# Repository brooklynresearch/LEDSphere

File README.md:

# LEDSphere
Code for controlling a matrix of LED Spheres

## Embedded Code
This folder is for any code that will be needed for the individual spheres

## Controller Code
This folder is for any code that will control full set of animations

## Eagle Files
This folder is for any PCB that will need to be designed for the spheres and control

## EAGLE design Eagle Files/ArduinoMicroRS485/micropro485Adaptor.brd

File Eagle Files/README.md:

# Eagle Files
CAD files for PCB Designs.  All designs are currently tailored for the othermill and are more or less a one layer.

## Pixel Controller
Files for the individual Sphere.

## ENC28J60
Files for the ENC28J60 Breakout

## PoE Supply
Files to convert the PoE power to +5V

## To Do
* Determine Communications Protocol
* Design for SMD components and reduce profile

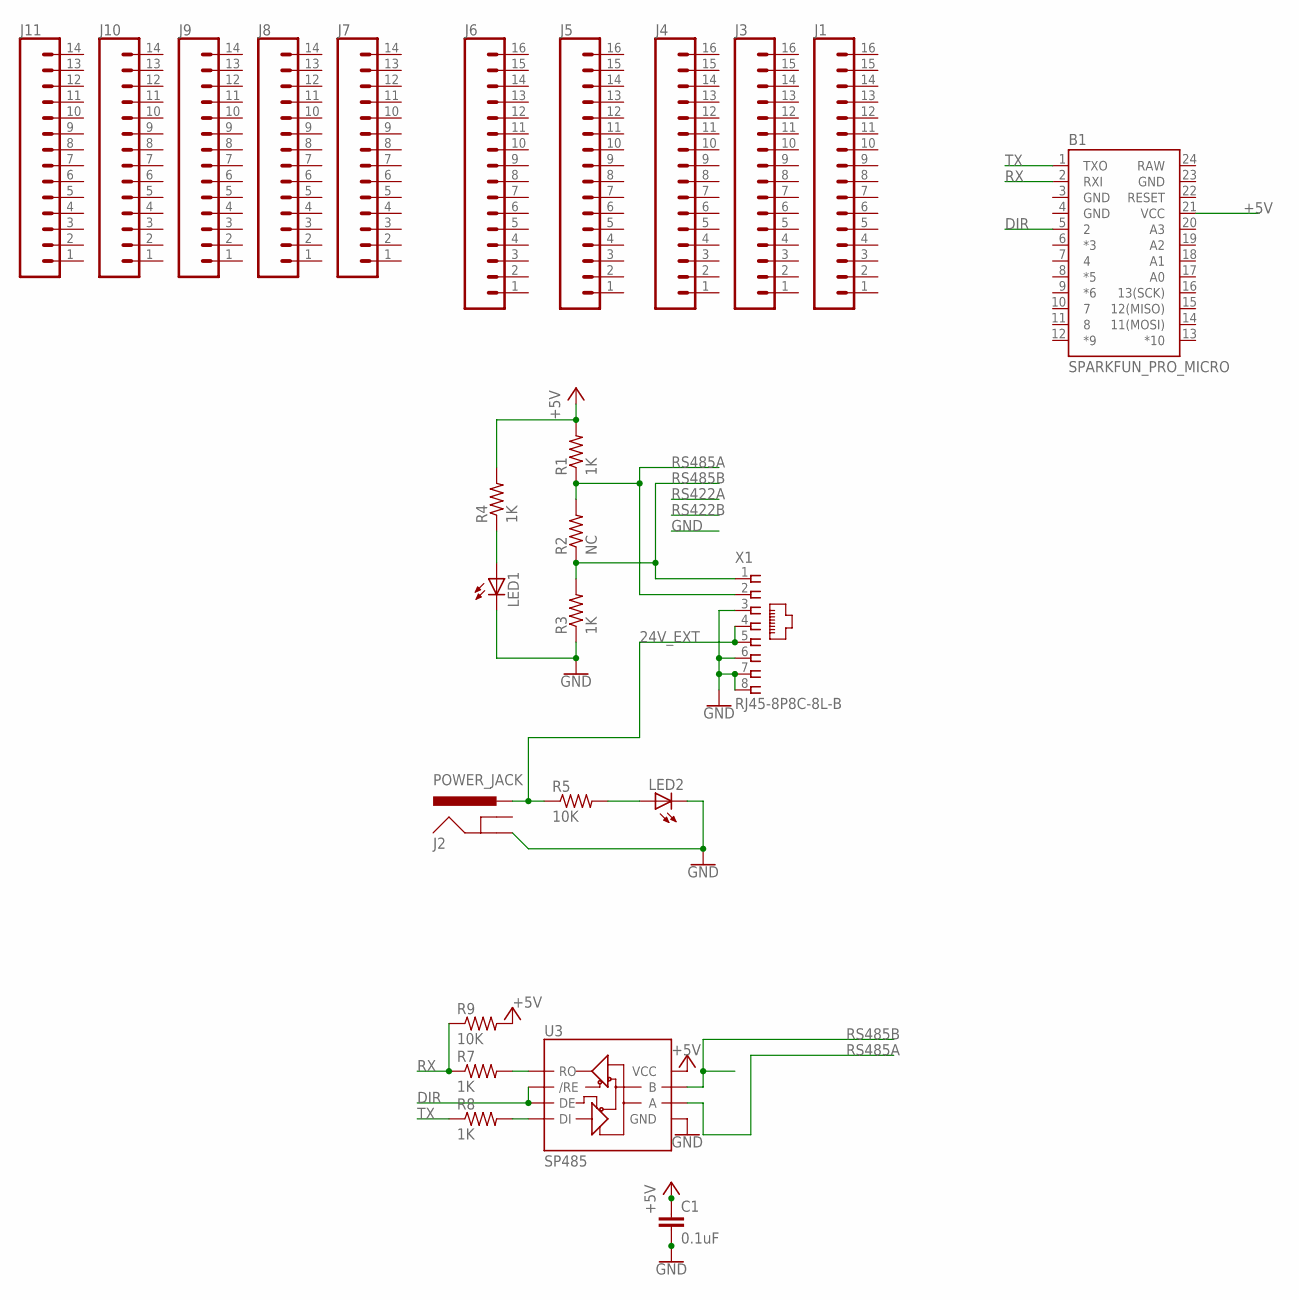
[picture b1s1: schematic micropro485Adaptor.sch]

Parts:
B1: SPARKFUN_PRO_MICRO
C1: 0.1uF; C0805K; LCSC C29926
J1, J3, J4, J5, J6: CONN_161X16_NO_SILK; 1X16_NO_SILK
J2: POWER_JACK; POWER_JACK_PTH
J7, J8, J9, J10, J11: CONN_14NO_SILK; 1X14_NO_SILK
LED1, LED2: LEDCHIP-LED0805; CHIP-LED0805
R1, R3, R4: 1K; R0805
R2: NC; R0805
R5, R9: 10K; R0805; LCSC C17414
R7, R8: 1K; R0805; LCSC C115316
U3: SP485; SO08; LCSC C6855
X1: RJ45-8P8C-8L-B; RJ45-SHIELD-DS1128-S80BP

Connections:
24V_EXT: J2.PWR, R5.1, X1.4, X1.5
+5V: B1.21 (VCC), C1.1, R1.2, R4.2, R9.2, U3.8 (VCC)
DIR: B1.5 (2), U3.2 (/RE), U3.3 (DE)
GND: B1.3 (GND), B1.4 (GND), B1.23 (GND), C1.2, J2.GND, LED1.C, LED2.C, R3.1, U3.5 (GND), X1.3, X1.6, X1.7, X1.8
unnamed: LED2.A, R5.2
unnamed: LED1.A, R4.1
unnamed: R7.2, U3.1 (RO)
unnamed: R8.2, U3.4 (DI)
RAW: B1.24 (RAW)
RS485A: R1.1, R2.2, U3.6 (A), X1.2
RS485B: R2.1, R3.2, U3.7 (B), X1.1
RX: B1.2 (RXI), R7.1, R9.1
TX: B1.1 (TXO), R8.1

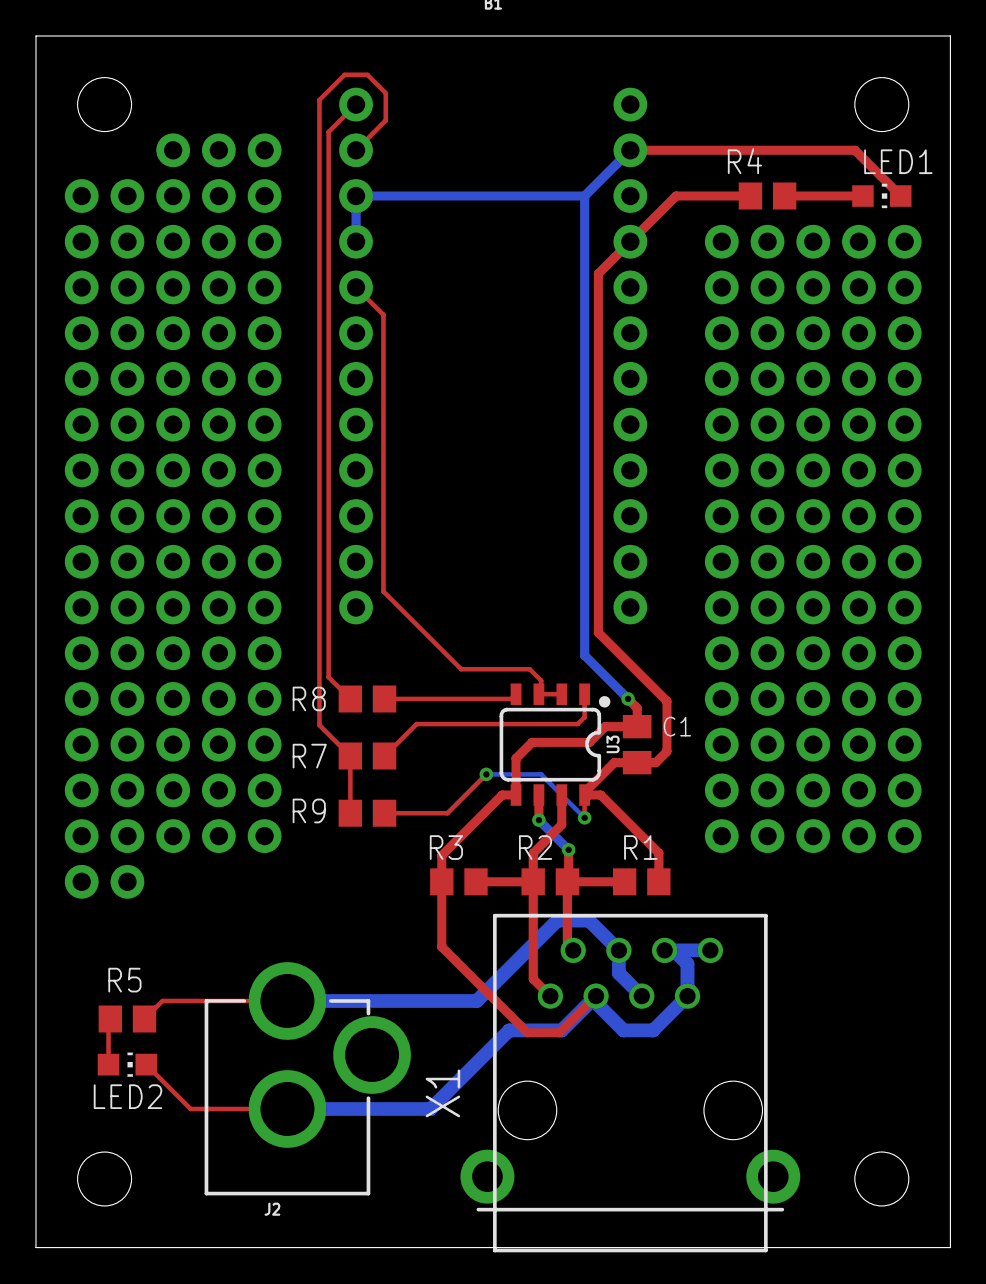
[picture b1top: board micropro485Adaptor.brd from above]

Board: 2 copper layers, 50.8 x 67.3 mm, 25 parts (0 on the bottom side), 12 nets.

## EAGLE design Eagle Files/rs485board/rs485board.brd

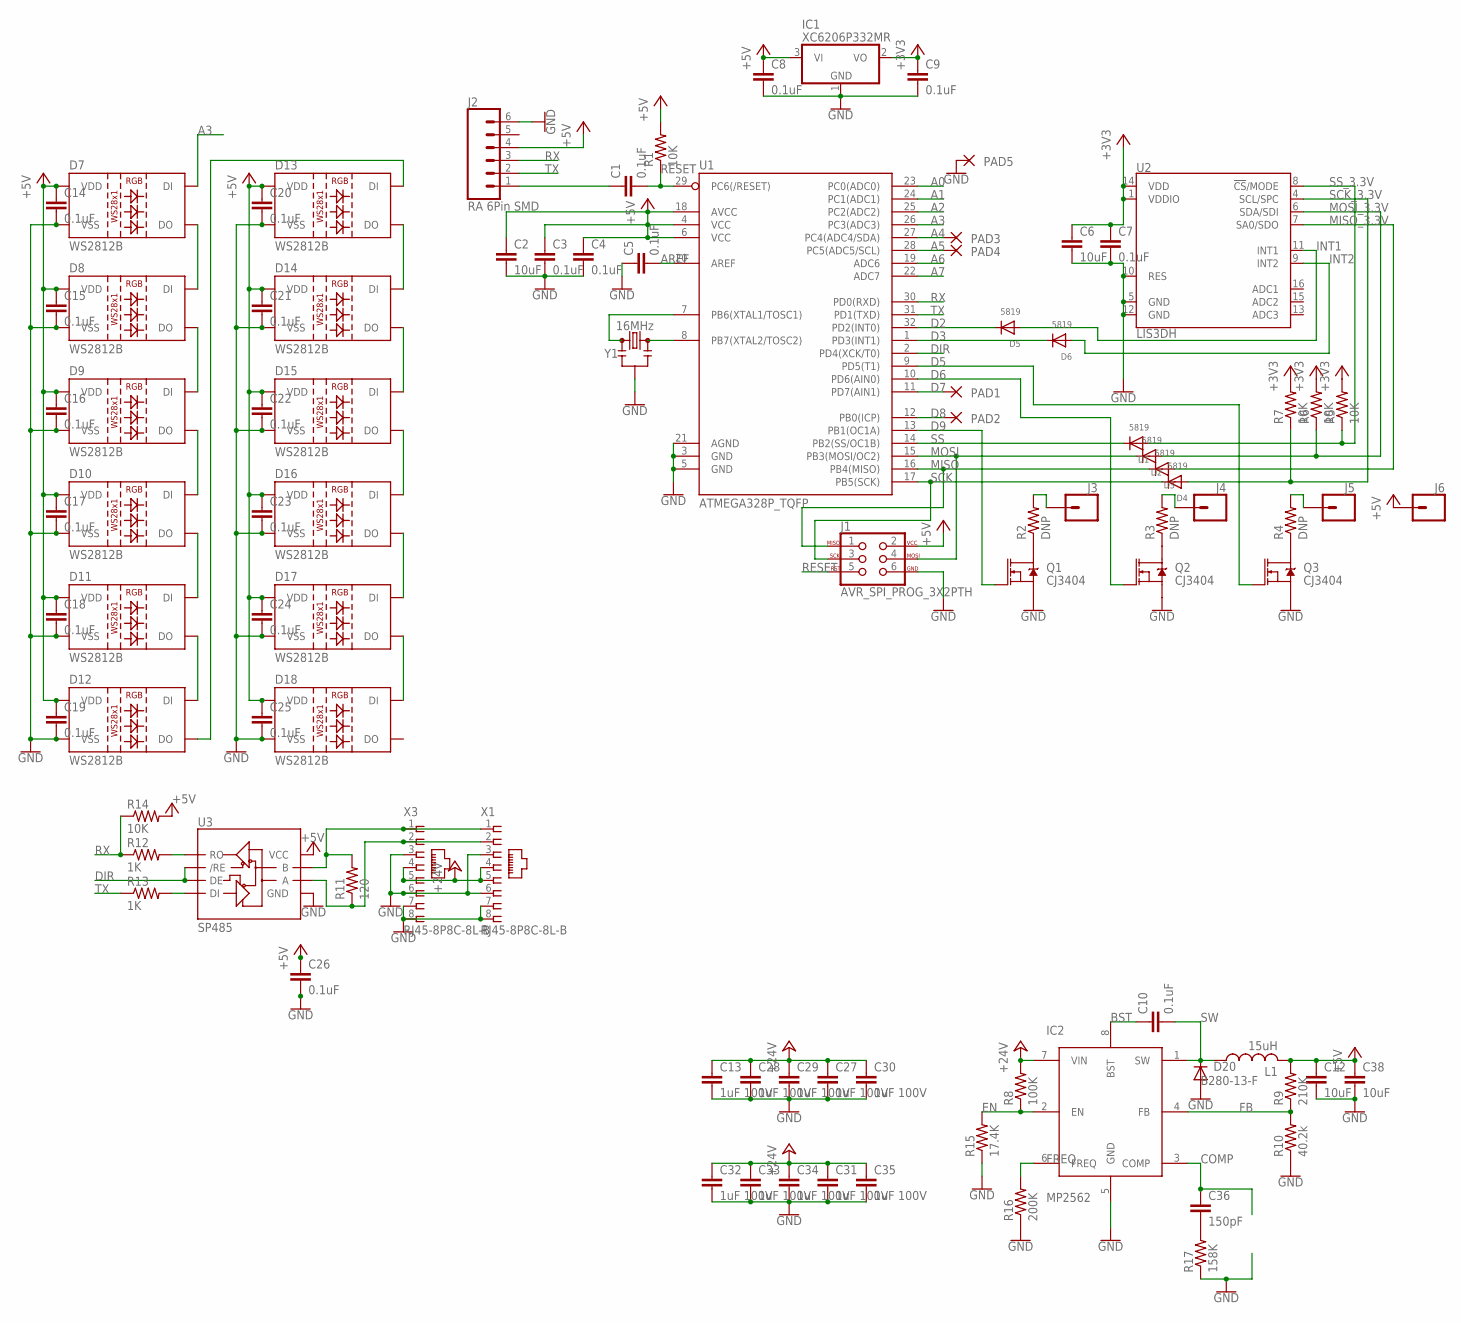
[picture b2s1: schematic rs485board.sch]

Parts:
C1, C3, C4, C5, C7, C8, C9, C10, C14, C15, C16, C17, C18, C19, C20, C21, C22, C23, C24, C25, C26: 0.1uF; C0805K; LCSC C29926
C2, C6, C12, C38: 10uF; C0805K; LCSC C92341
C13, C27, C28, C29, C30, C31, C32, C33, C34, C35: 1uF 100V; 1206; LCSC C91151
C36: 150pF; C0805K; LCSC C152846
D1, D2, D3, D4, D5, D6: 5819; SOD-123; LCSC C64885
D7, D8, D9, D10, D11, D12, D13, D14, D15, D16, D17, D18: WS2812B; LCSC C114585
D20: B280-13-F; DO214AA; LCSC C134445
IC1: XC6206P332MR; SOT23; LCSC C5446
IC2: MP2562; SO08; LCSC C93647
J1: AVR_SPI_PROG_3X2PTH; 2X3
J2: RA 6Pin SMD; 1X06-SMD_RA_MALE
J3, J4, J5, J6: CONN_01; 1X01
L1: 15uH; SLF12575; LCSC C136211
PAD1, PAD2, PAD3, PAD4, PAD5: 1,6/0,8
Q1, Q2, Q3: CJ3404; SOT23-3
R1, R5, R6, R7, R14: 10K; R0805; LCSC C17414
R2, R3, R4: DNP; R0805
R8: 100K; R0805; LCSC C96346
R9: 210K; R0805; LCSC C170839
R10: 40.2k; R0805; LCSC C104303
R11: 120; R0805
R12, R13: 1K; R0805; LCSC C115316
R15: 17.4K; R0805; LCSC C144583
R16: 200K; R0805; LCSC C17539
R17: 158K; R0805; LCSC C104013
U1: ATMEGA328P_TQFP; TQFP32-08; LCSC C14877
U2: LIS3DH; LGA-16-3X3; LCSC C15134
U3: SP485; SO08; LCSC C6855
X1, X3: RJ45-8P8C-8L-B; RJ45-SHIELD-DS1128-S80BP; LCSC C86586
Y1: 16MHz; RESONATOR-SMD-3.2X1.3; LCSC C91584

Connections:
+3V3: C6.1, C7.1, C9.1, IC1.2 (VO), R5.2, R6.2, R7.2, U2.1 (VDDIO), U2.14 (VDD)
+5V: C2.1, C3.1, C4.1, C8.1, C12.1, C14.1, C15.1, C16.1, C17.1, C18.1, C19.1, C20.1, C21.1, C22.1, C23.1, C24.1, C25.1, C26.1, C38.1, D7.1 (VDD), D8.1 (VDD), D9.1 (VDD), D10.1 (VDD), D11.1 (VDD), D12.1 (VDD), D13.1 (VDD), D14.1 (VDD), D15.1 (VDD), D16.1 (VDD), D17.1 (VDD), D18.1 (VDD), IC1.3 (VI), J1.2, J2.4, J6.1, L1.P$2 (2), R1.2, R9.2, R14.2, U1.4 (VCC), U1.6 (VCC), U1.18 (AVCC), U3.8 (VCC)
+24V: C13.1, C27.1, C28.1, C29.1, C30.1, C31.1, C32.1, C33.1, C34.1, C35.1, IC2.7 (VIN), R8.2, X1.4, X1.5, X3.4, X3.5
A0: U1.23 (PC0(ADC0))
A1: U1.24 (PC1(ADC1))
A2: U1.25 (PC2(ADC2))
A3: D7.4 (DI), U1.26 (PC3(ADC3))
A4: PAD3.1, U1.27 (PC4(ADC4/SDA))
A5: PAD4.1, U1.28 (PC5(ADC5/SCL))
A6: U1.19 (ADC6)
A7: U1.22 (ADC7)
AREF: C5.2, U1.20 (AREF)
BST: C10.1, IC2.8 (BST)
COMP: C36.1, IC2.3 (COMP)
D2: D5.C, U1.32 (PD2(INT0))
D3: D6.C, U1.1 (PD3(INT1))
D5: Q3.1 (G), U1.9 (PD5(T1))
D6: Q2.1 (G), U1.10 (PD6(AIN0))
D7: PAD1.1, U1.11 (PD7(AIN1))
D8: PAD2.1, U1.12 (PB0(ICP))
D9: Q1.1 (G), U1.13 (PB1(OC1A))
DIR: U1.2 (PD4(XCK/T0)), U3.2 (/RE), U3.3 (DE)
EN: IC2.2 (EN), R8.1, R15.2
FB: IC2.4 (FB), R9.1, R10.2
FREQ: IC2.6 (FREQ), R16.2
GND: C2.2, C3.2, C4.2, C5.1, C6.2, C7.2, C8.2, C9.2, C12.2, C13.2, C14.2, C15.2, C16.2, C17.2, C18.2, C19.2, C20.2, C21.2, C22.2, C23.2, C24.2, C25.2, C26.2, C27.2, C28.2, C29.2, C30.2, C31.2, C32.2, C33.2, C34.2, C35.2, C38.2, D7.3 (VSS), D8.3 (VSS), D9.3 (VSS), D10.3 (VSS), D11.3 (VSS), D12.3 (VSS), D13.3 (VSS), D14.3 (VSS), D15.3 (VSS), D16.3 (VSS), D17.3 (VSS), D18.3 (VSS), D20.A, IC1.1 (GND), IC2.5 (GND), J1.6, J2.6, PAD5.1, Q1.2 (S), Q2.2 (S), Q3.2 (S), R10.1, R15.1, R16.1, R17.1, U1.3 (GND), U1.5 (GND), U1.21 (AGND), U2.5 (GND), U2.10 (RES), U2.12 (GND), U3.5 (GND), X1.3, X1.6, X1.7, X1.8, X3.3, X3.6, X3.7, X3.8, Y1.2
INT1: D5.A, U2.11 (INT1)
INT2: D6.A, U2.9 (INT2)
MISO: D3.C, J1.1, U1.16 (PB4(MISO))
MISO_3.3V: D3.A, U2.7 (SA0/SDO)
MOSI: D2.C, J1.4, U1.15 (PB3(MOSI/OC2))
MOSI_3.3V: D2.A, R6.1, U2.6 (SDA/SDI)
unnamed: Q1.3 (D), R2.1
unnamed: D7.2 (DO), D8.4 (DI)
unnamed: D8.2 (DO), D9.4 (DI)
unnamed: J3.1, R2.2
unnamed: Q2.3 (D), R3.1
unnamed: J4.1, R3.2
unnamed: Q3.3 (D), R4.1
unnamed: J5.1, R4.2
unnamed: D9.2 (DO), D10.4 (DI)
unnamed: D10.2 (DO), D11.4 (DI)
unnamed: D11.2 (DO), D12.4 (DI)
unnamed: D12.2 (DO), D13.4 (DI)
unnamed: D13.2 (DO), D14.4 (DI)
unnamed: D14.2 (DO), D15.4 (DI)
unnamed: D15.2 (DO), D16.4 (DI)
unnamed: D16.2 (DO), D17.4 (DI)
unnamed: D17.2 (DO), D18.4 (DI)
unnamed: C36.2, R17.2
unnamed: R12.2, U3.1 (RO)
unnamed: R13.2, U3.4 (DI)
RESET: C1.2, J1.5, R1.1, U1.29 (PC6(/RESET))
RESET_EXT: C1.1, J2.1
RS485A: R11.1, U3.6 (A), X1.2, X3.2
RS485B: R11.2, U3.7 (B), X1.1, X3.1
RX: J2.3, R12.1, R14.1, U1.30 (PD0(RXD))
SCK: D4.C, J1.3, U1.17 (PB5(SCK))
SCK_3.3V: D4.A, R7.1, U2.4 (SCL/SPC)
SS: D1.C, U1.14 (PB2(SS/OC1B))
SS_3.3V: D1.A, R5.1, U2.8 (!CS!/MODE)
SW: C10.2, D20.C, IC2.1 (SW), L1.P$1 (1)
TX: J2.2, R13.1, U1.31 (PD1(TXD))
XTAL1: U1.7 (PB6(XTAL1/TOSC1)), Y1.1
XTAL2: U1.8 (PB7(XTAL2/TOSC2)), Y1.3

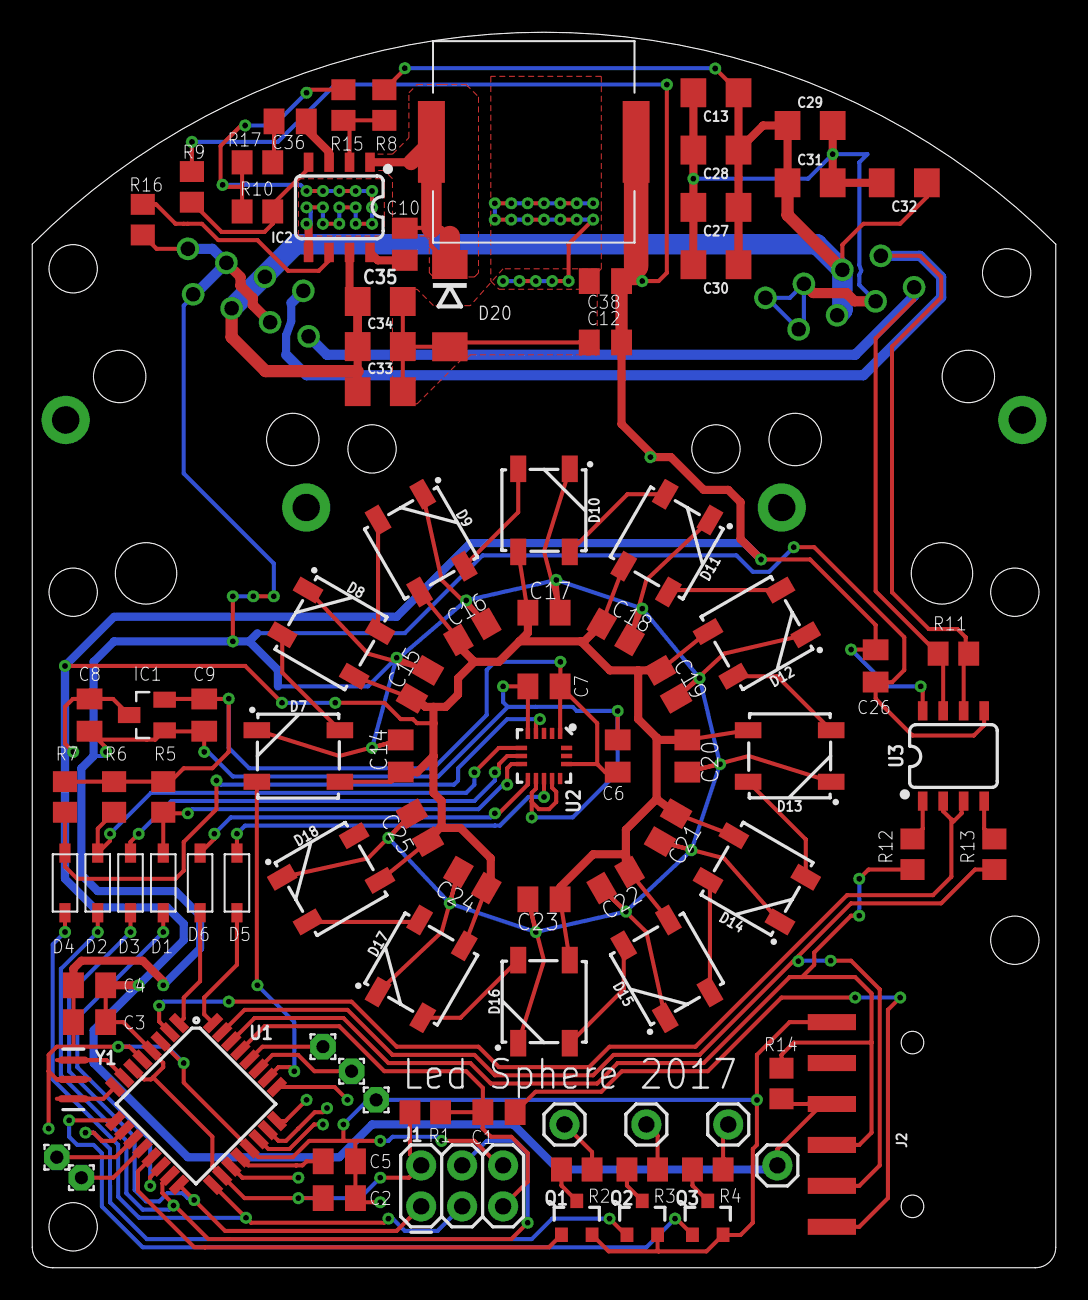
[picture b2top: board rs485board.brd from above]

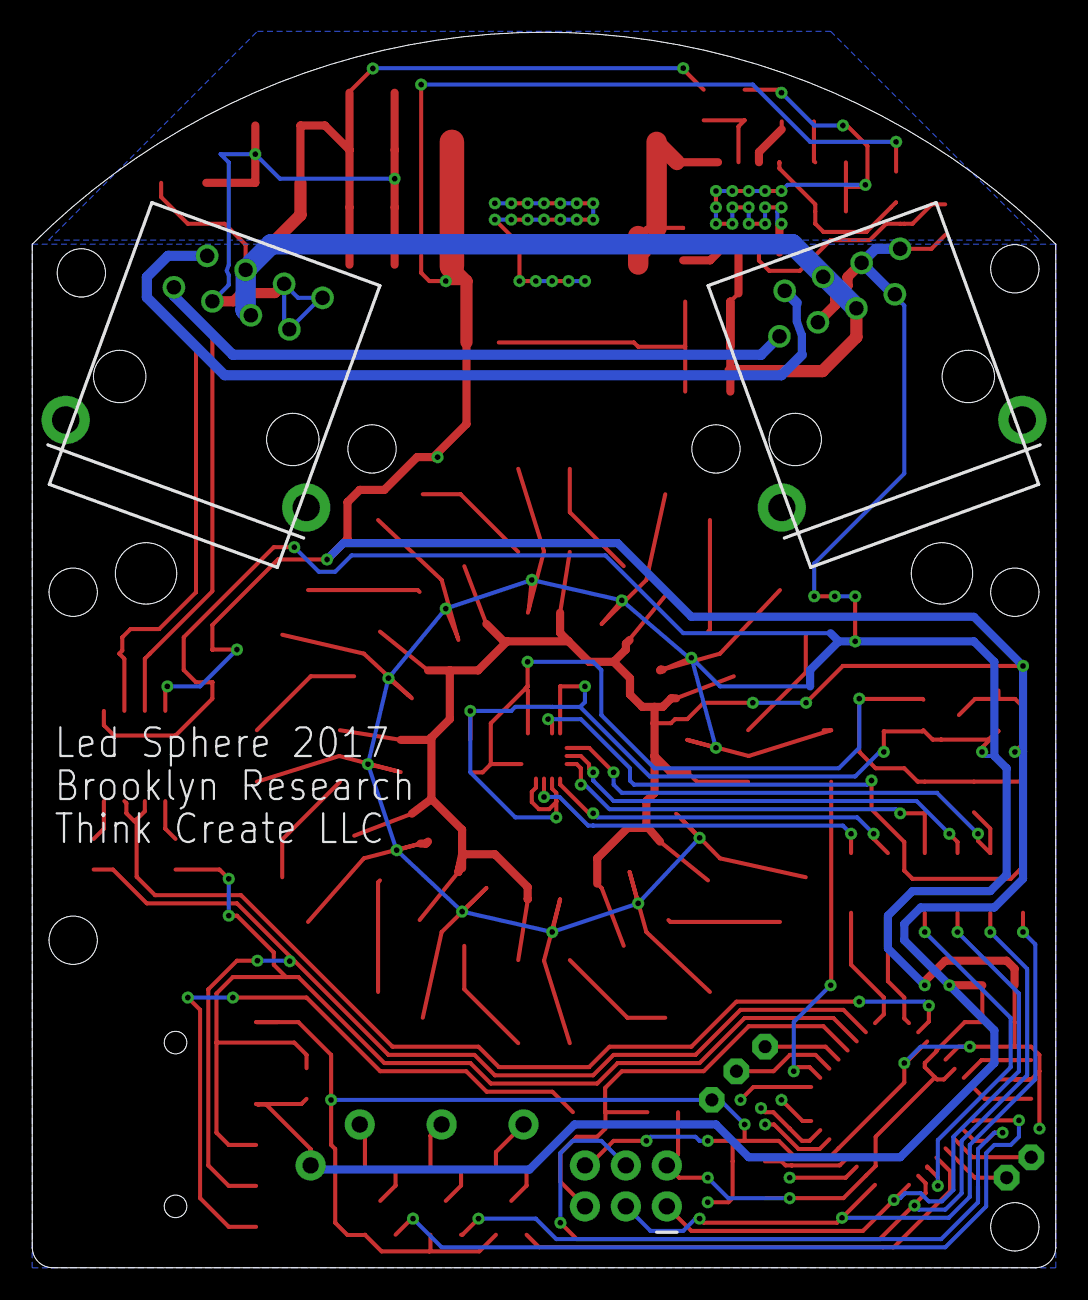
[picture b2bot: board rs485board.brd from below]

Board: 2 copper layers, 63.5 x 76.7 mm, 95 parts (2 on the bottom side), 60 nets.

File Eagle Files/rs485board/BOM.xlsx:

Qty | Value | Device | Package | Parts | Description | LCSC | MF | MPN | OC_FARNELL | OC_NEWARK | PROD_ID | SF_ID | VALUE
5 |  | 1,6/0,8 | 1,6/0,8 | PAD1, PAD2, PAD3, PAD4, PAD5 | THROUGH-HOLE PAD
4 |  | CONN_01 | 1X01 | J3, J4, J5, J6 | Single connection point. Often used as Generic Header-pin footprint for 0.1 inc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
21 | 0.1uF | C-EUC0805K | C0805K | C1, C3, C4, C5, C7, C8, C9, C10, C14, C15, C16, C17, C18, C19, C20, C21, C22, C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 | CAPACITOR, European symbol | C29926
1 | 100K | R-US_R0805 | R0805 | R8 | RESISTOR, American symbol | C96346
5 | 10K | R-US_R0805 | R0805 | R1, R5, R6, R7, R14 | RESISTOR, American symbol | C17414
4 | 10uF | C-EUC0805K | C0805K | C2, C6, C12, C38 | CAPACITOR, European symbol | C92341
1 | 120 | R-US_R0805 | R0805 | R11 | RESISTOR, American symbol
1 | 150pF | C-EUC0805K | C0805K | C36 | CAPACITOR, European symbol | C152846
1 | 158K | R-US_R0805 | R0805 | R17 | RESISTOR, American symbol | C104013
1 | 15uH | SLF12575T | SLF12575 | L1 |  | C136211
1 | 16MHz | RESONATOR-16MHZSMD_3.2X1.3 | RESONATOR-SMD-3.2X1.3 | Y1 | 16MHz Resonator | C91584 |  |  |  |  | XTAL-08900 |  | 16MHz
1 | 17.4K | R-US_R0805 | R0805 | R15 | RESISTOR, American symbol | C144583
2 | 1K | R-US_R0805 | R0805 | R12, R13 | RESISTOR, American symbol | C115316
10 | 1uF 100V | 10UF-1206-6.3V-20% | 1206 | C13, C27, C28, C29, C30, C31, C32, C33, C34, C35 | 10.0¬µF ceramic capacitors | C91151 |  |  |  |  | CAP-10057 |  | 10uF
1 | 200K | R-US_R0805 | R0805 | R16 | RESISTOR, American symbol | C17539
1 | 210K | R-US_R0805 | R0805 | R9 | RESISTOR, American symbol | C170839
1 | 40.2k | R-US_R0805 | R0805 | R10 | RESISTOR, American symbol | C104303
6 | 5819 | DIODESOD-123 | SOD-123 | D1, D2, D3, D4, D5, D6 | Diode | C64885
1 | ATMEGA328P_TQFP | ATMEGA328P_TQFP | TQFP32-08 | U1 | Popular 328P in QFP | C14877 |  |  |  |  | IC-09069 |  | ATMEGA328P_TQFP
1 | AVR_SPI_PROG_3X2PTH | AVR_SPI_PROG_3X2PTH | 2X3 | J1 | AVR ISP 6 Pin
1 | B280-13-F | DIODE-DO214AA | DO214AA | D20 | DIODE | C134445
3 | CJ3404 | MOSFET-NCH-AO3404A | SOT23-3 | Q1, Q2, Q3 | N-channel MOSFETs |  |  |  |  |  | TRANS-12988 |  | 5.8A/30V/35mŒ©
3 | DNP | R-US_R0805 | R0805 | R2, R3, R4 | RESISTOR, American symbol
1 | LIS3DH | LIS3DH | LGA-16-3X3 | U2 | ST Microelectronics LIS3DH 3-Axis +/-2/4/8/16g SPI/I2C Accelerometer | C15134 |  |  |  |  | IC-13419 | N/A
1 | MP2562 | MP2562 | SO08 | IC2 |  | C93647
1 | RA 6Pin SMD | CONN_06SMD | 1X06-SMD_RA_MALE | J2 | Multi connection point. Often used as Generic Header-pin footprint for 0.1 inch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 |  |  |  |  |  | CONN-08971 |  | RA 6Pin SMD
2 | RJ45-8P8C-8L-B | RJ45-8P8C-8L-B | RJ45-SHIELD-DS1128-S80BP | X1, X3 | CORCOM Modular RJ Jacks No Shield | C86586 | TYCO ELECTRONICS | RJ45-8L-B | 1279843 | 52K4445
1 | SP485 | RS485SOIC | SO08 | U3 | RS-485 Transceiver | C6855 |  |  |  |  | IC-09388 |  | MAX3485CSA
12 | WS2812B | WS2812B | WS2812B | D7, D8, D9, D10, D11, D12, D13, D14, D15, D16, D17, D18 | WS2812B SMD addressable RGB LED | C114585 |  |  |  |  | DIO-12503 |  | WS2812B
1 | XC6206P332MR | MCP1703CB | SOT23 | IC1 | 250 mA, 16V, Low Quiescent Current LDO Regulator | C5446

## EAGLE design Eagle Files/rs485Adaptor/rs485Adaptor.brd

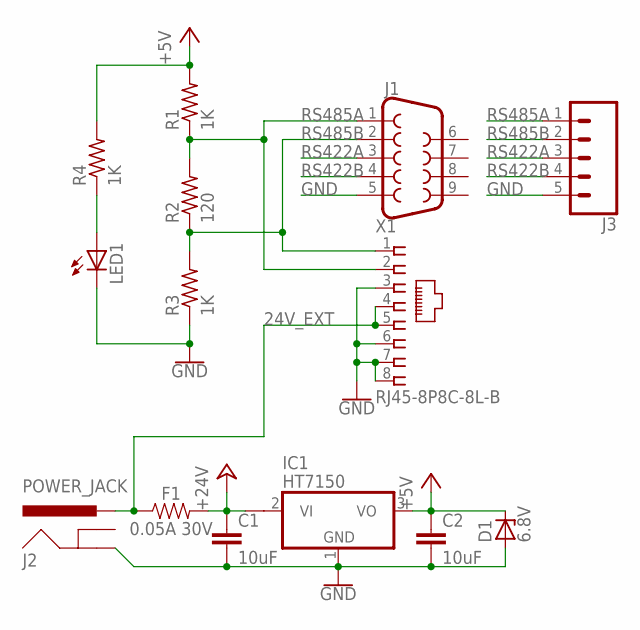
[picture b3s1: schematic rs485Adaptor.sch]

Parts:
C1: 10uF; 1206
C2: 10uF; C0805K
D1: 6.8V; SOD80C
F1: 0.05A 30V; 1210
IC1: HT7150; SOT89
J1: DB9FEMALE; DB9
J2: POWER_JACK; POWER_JACK_PTH
J3: CONN_05SCREW; SCREWTERMINAL-3.5MM-5
LED1: LEDCHIP-LED0805; CHIP-LED0805
R1, R3, R4: 1K; R0805
R2: 120; R0805
X1: RJ45-8P8C-8L-B; RJ45-SHIELD-DS1128-S80BP

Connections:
24V_EXT: F1.1, J2.PWR, X1.4, X1.5
+5V: C2.1, D1.C, IC1.3 (VO), R1.2, R4.2
+24V: C1.1, F1.2, IC1.2@1 (VI1)
GND: C1.2, C2.2, D1.A, IC1.1 (GND), J1.5, J2.GND, J3.5, LED1.C, R3.1, X1.3, X1.6, X1.7, X1.8
unnamed: LED1.A, R4.1
RS422A: J1.3, J3.3
RS422B: J1.4, J3.4
RS485A: J1.1, J3.1, R1.1, R2.2, X1.2
RS485B: J1.2, J3.2, R2.1, R3.2, X1.1

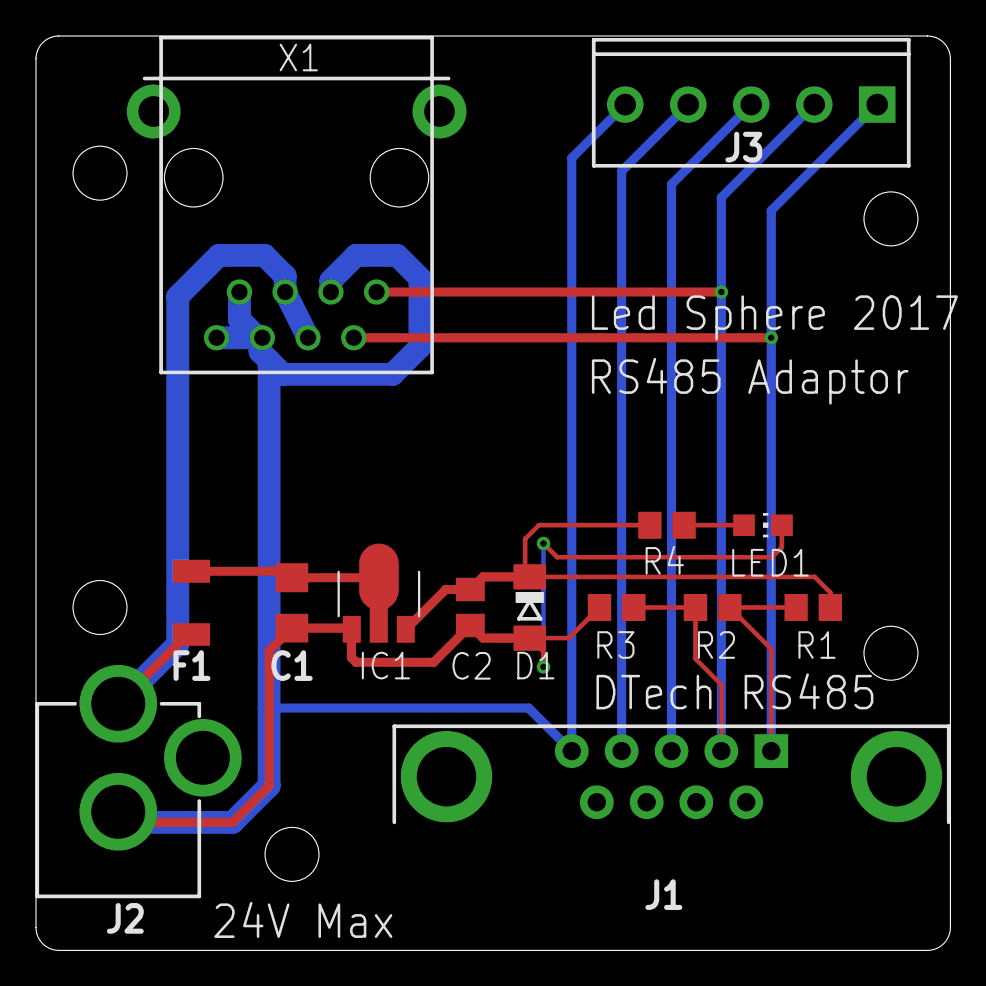
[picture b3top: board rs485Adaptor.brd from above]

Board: 2 copper layers, 50.8 x 50.8 mm, 14 parts (0 on the bottom side), 9 nets.

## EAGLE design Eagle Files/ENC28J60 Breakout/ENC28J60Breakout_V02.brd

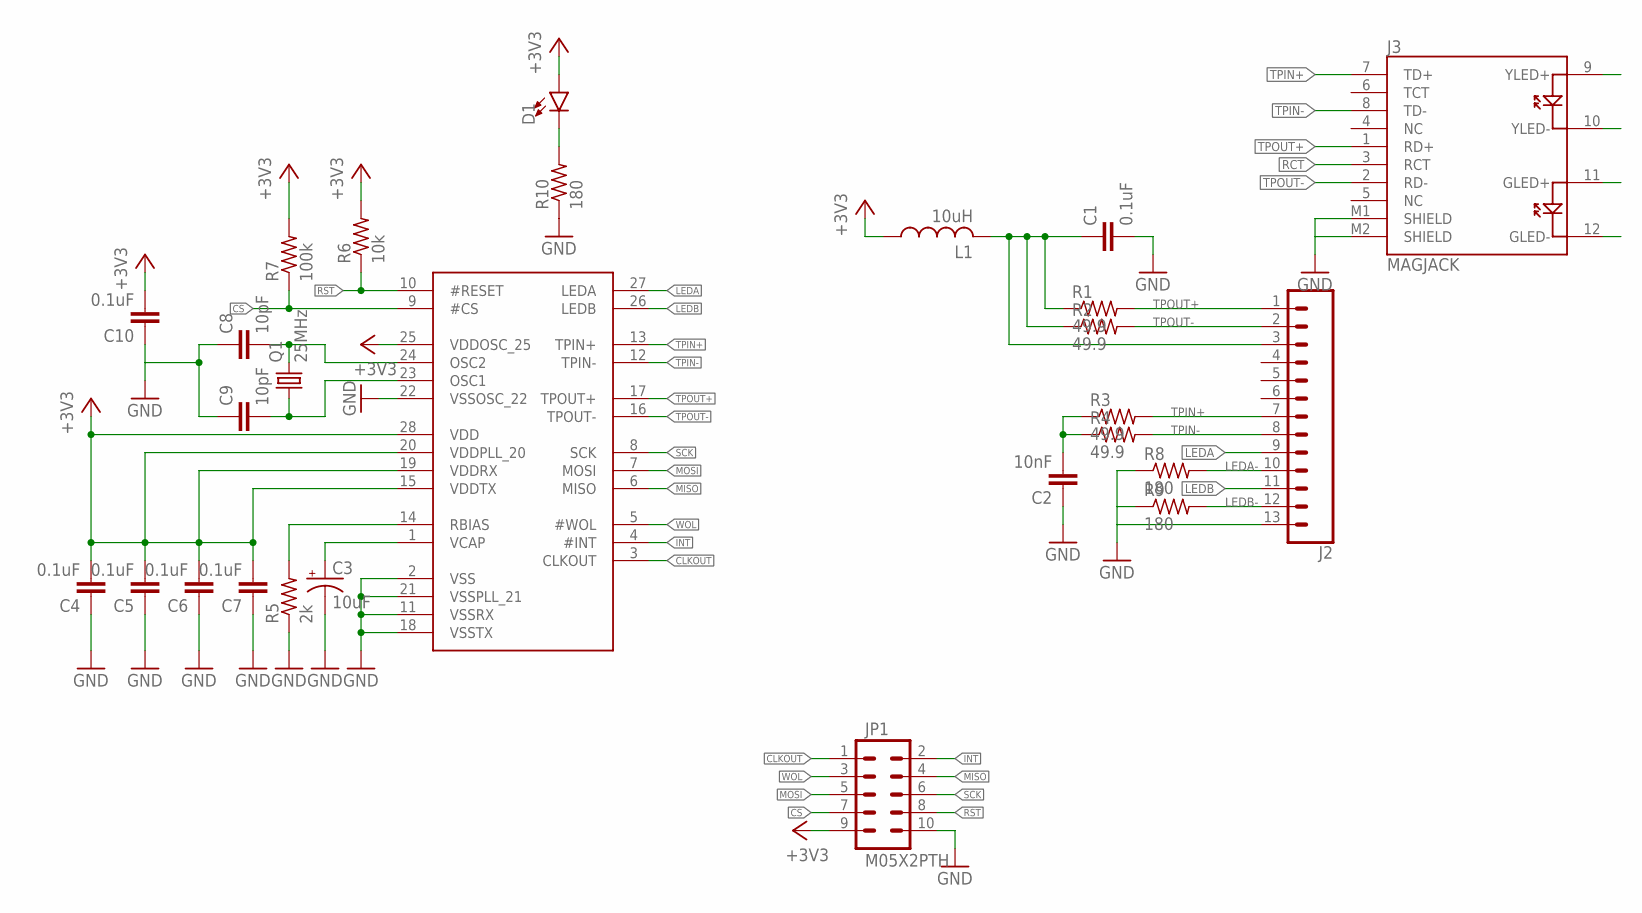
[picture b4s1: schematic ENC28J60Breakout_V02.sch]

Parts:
C1, C4, C5, C6, C7, C10: 0.1uF; C050-024X044
C2: 10nF; C050-024X044
C3: 10uF; E2,5-7
C8, C9: 10pF; C050-024X044
D1: LED5MM; LED_5MM
J2: CONN_13; 1X13
J3: MAGJACK
JP1: M05X2PTH; AVR_ICSP
L1: 10uH; 0204/7
Q1: 25MHz; HC49/S
R1, R2, R3, R4: 49.9; 0204/7
R5: 2k; 0204/7
R6: 10k; 0204/7
R7: 100k; 0204/7
R8, R9, R10: 180; 0204/7
U$1: ENC28J60; ENC28J60_DIP

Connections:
+3V3: C4.2, C5.2, C6.2, C7.2, C10.2, D1.A, JP1.9, L1.1, R6.2, R7.2, U$1.15 (VDDTX), U$1.19 (VDDRX), U$1.20 (VDDPLL_20), U$1.25 (VDDOSC_25), U$1.28 (VDD)
CLKOUT: JP1.1, U$1.3 (CLKOUT)
CS: JP1.7, R7.1, U$1.9 (#CS)
GND: C1.2, C2.1, C3.-, C4.1, C5.1, C6.1, C7.1, C8.1, C9.1, C10.1, J2.13, J3.M1 (SHIELD), J3.M2 (SHIELD), JP1.10, R5.1, R8.1, R9.1, R10.1, U$1.2 (VSS), U$1.11 (VSSRX), U$1.18 (VSSTX), U$1.21 (VSSPLL_21), U$1.22 (VSSOSC_22)
INT: JP1.2, U$1.4 (#INT)
LEDA: J2.9, J3.9 (YLED+), U$1.27 (LEDA)
LEDA-: J2.10, J3.10 (YLED-), R8.2
LEDB: J2.11, J3.11 (GLED+), U$1.26 (LEDB)
LEDB-: J2.12, J3.12 (GLED-), R9.2
MISO: JP1.4, U$1.6 (MISO)
MOSI: JP1.5, U$1.7 (MOSI)
unnamed: C8.2, Q1.2, U$1.24 (OSC2)
unnamed: D1.K (C), R10.2
unnamed: C9.2, Q1.1, U$1.23 (OSC1)
unnamed: C3.+, U$1.1 (VCAP)
unnamed: R5.2, U$1.14 (RBIAS)
unnamed: C2.2, R3.1, R4.1
RCT: C1.1, J2.3, J3.3 (RCT), L1.2, R1.1, R2.1
RST: JP1.8, R6.1, U$1.10 (#RESET)
SCK: JP1.6, U$1.8 (SCK)
TPIN+: J2.7, J3.7 (TD+), R3.2, U$1.13 (TPIN+)
TPIN-: J2.8, J3.8 (TD-), R4.2, U$1.12 (TPIN-)
TPOUT+: J2.1, J3.1 (RD+), R1.2, U$1.17 (TPOUT+)
TPOUT-: J2.2, J3.2 (RD-), R2.2, U$1.16 (TPOUT-)
WOL: JP1.3, U$1.5 (#WOL)

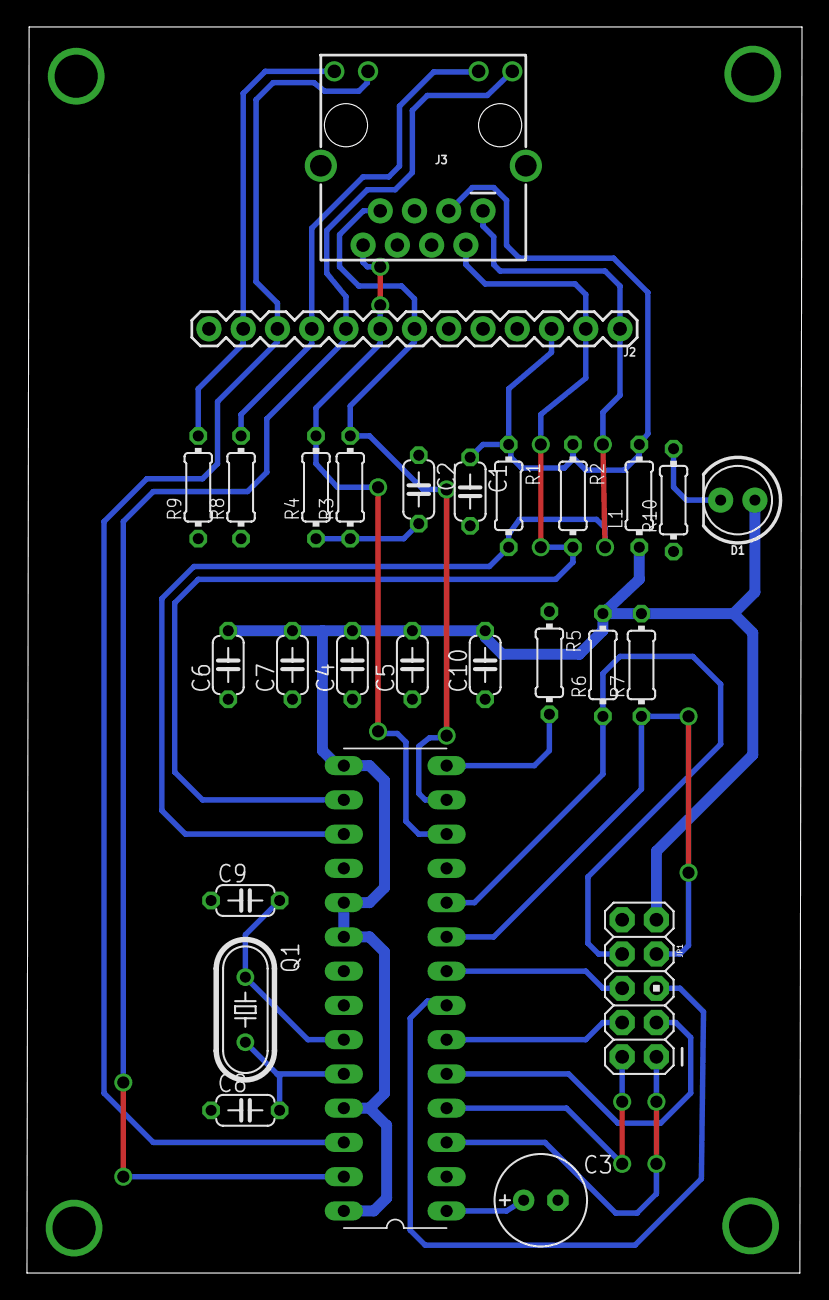
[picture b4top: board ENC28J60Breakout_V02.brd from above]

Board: 2 copper layers, 57.5 x 92.4 mm, 27 parts (0 on the bottom side), 25 nets.

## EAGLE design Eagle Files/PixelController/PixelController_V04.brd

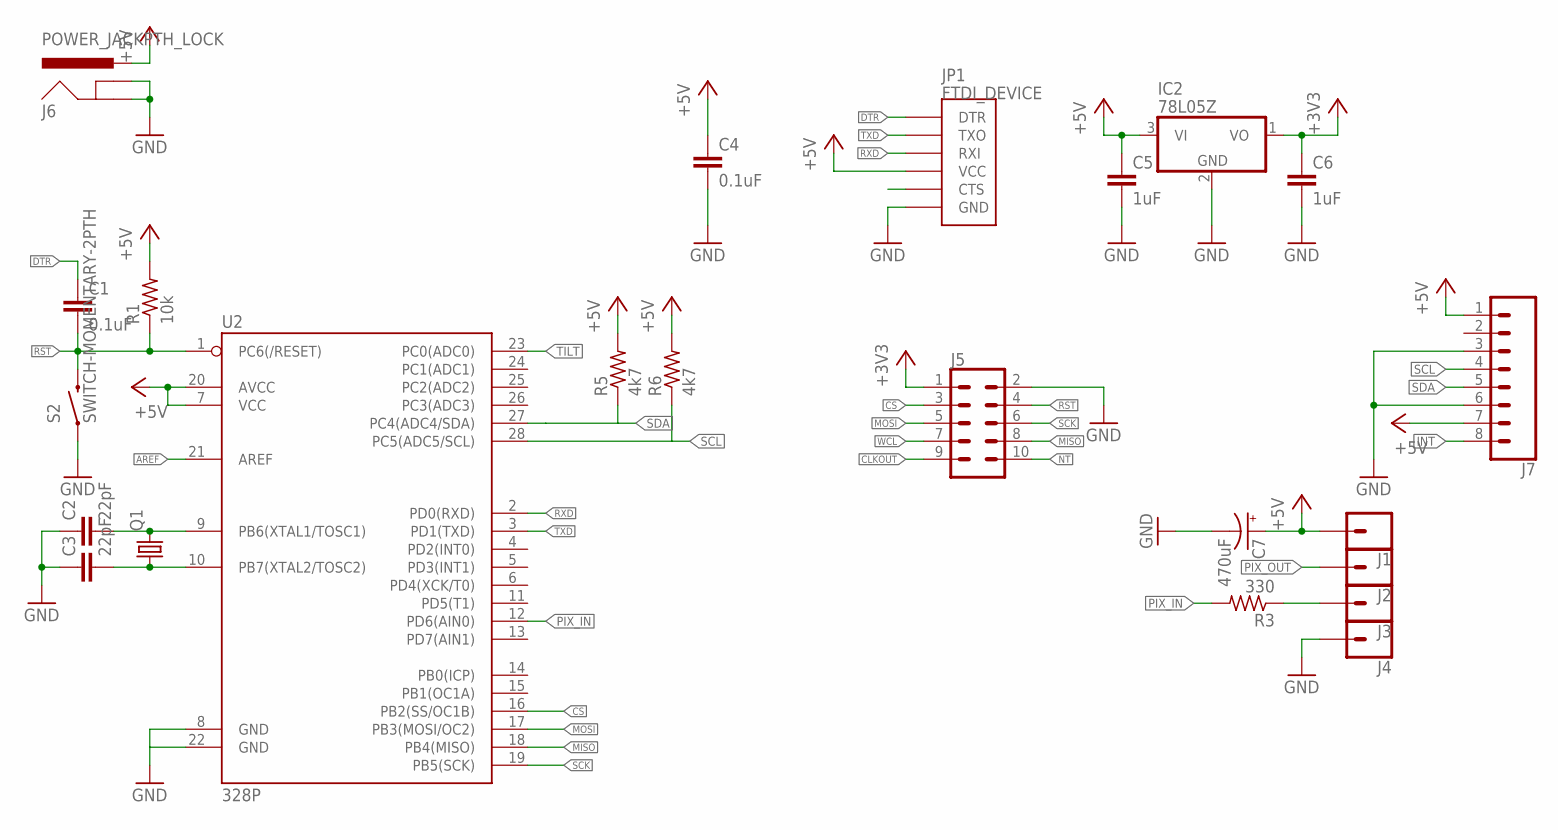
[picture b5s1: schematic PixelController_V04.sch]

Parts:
C1, C4: 0.1uF; C050-025X075
C2, C3: 22pF; C050-024X044
C5, C6: 1uF; C050-025X075
C7: 470uF; E3,5-8
IC2: 78L05Z; TO92
J1, J2, J3, J4: CONN_01; 1X01
J5: CONN_05X2PTH; 2X5
J6: POWER_JACKPTH_LOCK; POWER_JACK_PTH_LOCK
J7: CONN_08"; 1X08@1
JP1: FTDI_DEVICE; FTDI_DEVICE_SIDE
Q1: CRYSTALHC49U70; HC49U70
R1: 10k; 0204/7
R3: 330; 0204/7
R5, R6: 4k7; 0204/7
S2: SWITCH-MOMENTARY-2PTH; TACTILE-PTH
U2: 328P; DIP28

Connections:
+3V3: C6.1, IC2.1 (VO), J5.1
+5V: C4.1, C5.1, C7.+, IC2.3 (VI), J1.1, J6.PWR, J7.1, J7.7, JP1.P$4 (VCC), R1.2, R5.2, R6.2, U2.7 (VCC), U2.20 (AVCC)
AREF: U2.21 (AREF)
CLKOUT: J5.9
CS: J5.3, U2.16 (PB2(SS/OC1B))
DTR: C1.1, JP1.P$1 (DTR)
GND: C2.1, C3.1, C4.2, C5.2, C6.2, C7.-, IC2.2 (GND), J4.1, J5.2, J6.GND, J6.GNDBREAK, J7.3, J7.6, JP1.P$6 (GND), S2.1, U2.8 (GND), U2.22 (GND)
INT: J7.8
MISO: J5.8, U2.18 (PB4(MISO))
MOSI: J5.5, U2.17 (PB3(MOSI/OC2))
unnamed: C3.2, Q1.1, U2.10 (PB7(XTAL2/TOSC2))
unnamed: C2.2, Q1.2, U2.9 (PB6(XTAL1/TOSC1))
unnamed: J3.1, R3.1
NT: J5.10
PIX_IN: R3.2, U2.12 (PD6(AIN0))
PIX_OUT: J2.1
RST: C1.2, J5.4, R1.1, S2.3 (2), U2.1 (PC6(/RESET))
RXD: JP1.P$3 (RXI), U2.2 (PD0(RXD))
SCK: J5.6, U2.19 (PB5(SCK))
SCL: J7.4, R6.1, U2.28 (PC5(ADC5/SCL))
SDA: J7.5, R5.1, U2.27 (PC4(ADC4/SDA))
TILT: U2.23 (PC0(ADC0))
TXD: JP1.P$2 (TXO), U2.3 (PD1(TXD))
WCL: J5.7

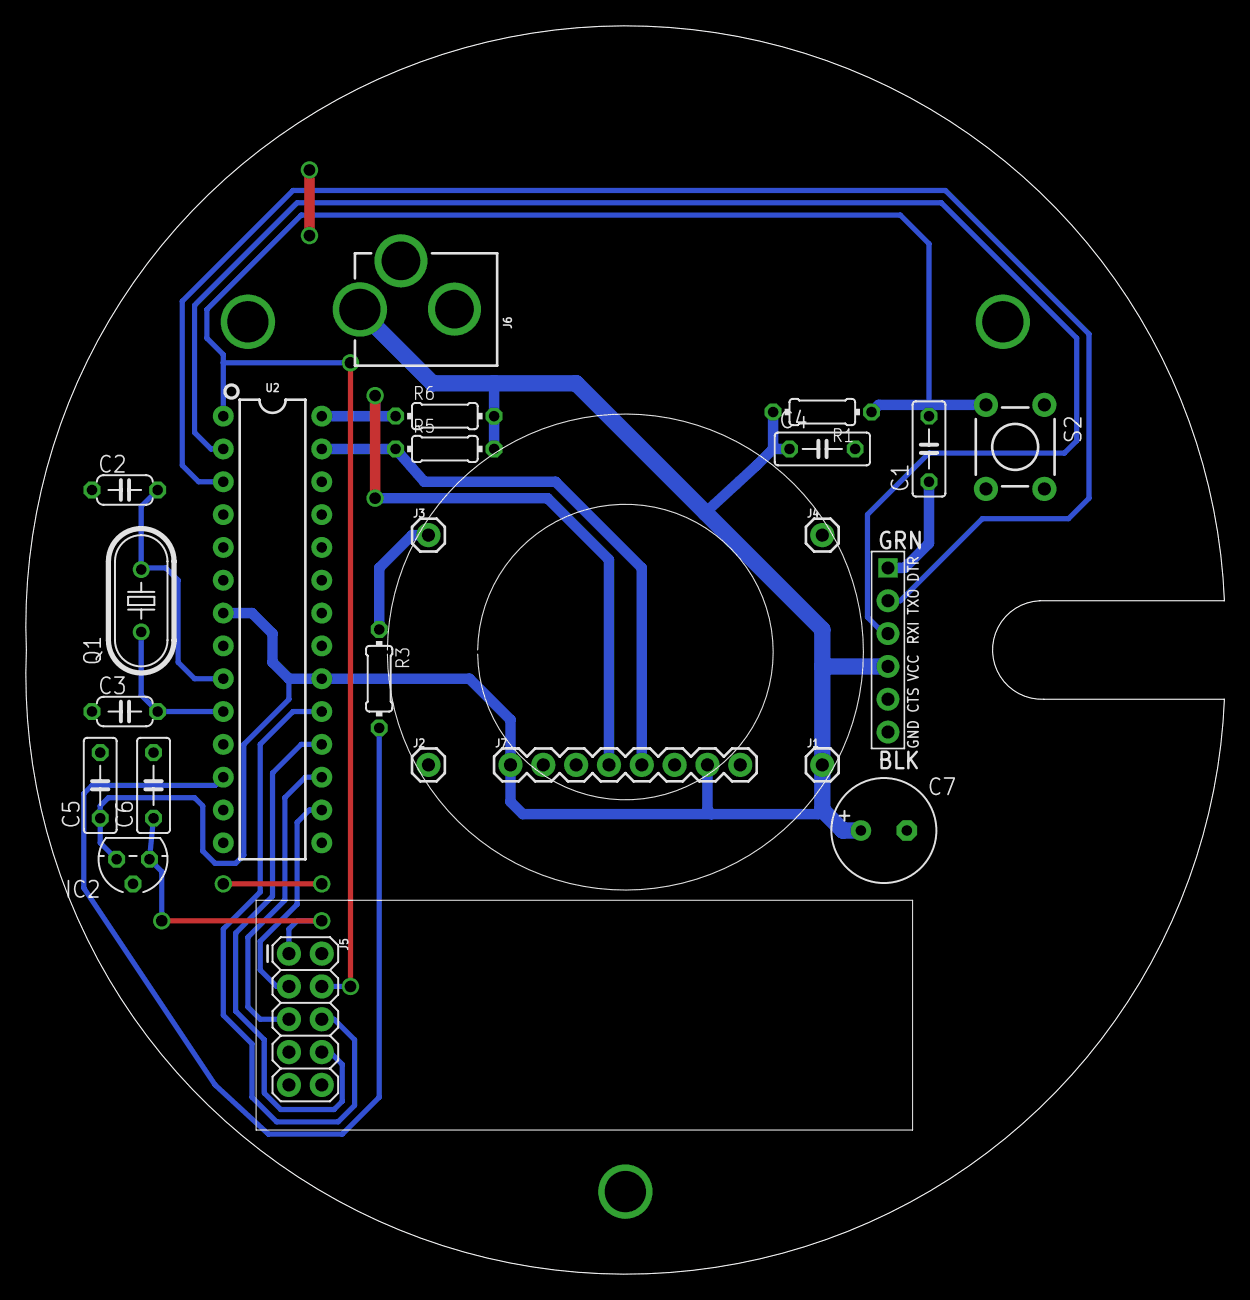
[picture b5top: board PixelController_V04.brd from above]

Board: 2 copper layers, 92.7 x 96.6 mm, 23 parts (0 on the bottom side), 17 nets.

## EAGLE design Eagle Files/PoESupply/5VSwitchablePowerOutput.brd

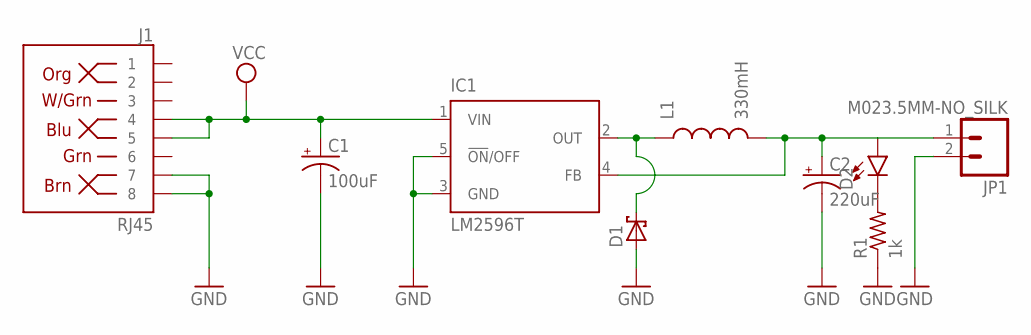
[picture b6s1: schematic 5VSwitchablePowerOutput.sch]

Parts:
C1: 100uF; E5-13
C2: 220uF; E3,5-10
D1: SCHOTTKY-DIODECB417-15; CB417-15
D2: LED5MM; LED_5MM
IC1: LM2596T; T05D
J1: RJ45; RJ45-8
JP1: M023.5MM-NO_SILK; SCREWTERMINAL-3.5MM-2-NS
L1: 330mH; RLB0912
R1: 1k; 0204/7

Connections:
GND: C1.-, C2.-, D1.A, IC1.3 (GND), IC1.5 (!ON!/OFF), J1.7, J1.8, JP1.2, R1.1
unnamed: D1.C, IC1.2 (OUT), L1.1
unnamed: C2.+, D2.A, IC1.4 (FB), JP1.1, L1.2
unnamed: D2.K (C), R1.2
VCC: C1.+, IC1.1 (VIN), J1.4, J1.5

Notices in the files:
parts and their libraries:
SparkFun-Boards: Licensing: Creative Commons ShareAlike 4.0 International - https://creativecommons.org/licenses/by-sa/4.0
SparkFun-Connectors: Licensing: CC v3.0 Share-Alike You are welcome to use this library for commercial purposes.
